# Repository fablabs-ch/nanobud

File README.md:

# Description
NanoBud is a simple electronic project created for workshops into FabLabs.
Basically this project is provided with "Space Invaders" retro game made by makestuffordie.
With simple electronic components you can make some great stuffs.
But you can use it not only for gaming. 
Per example, replace the rotary encoder by a temperature sensor, load the suitable arduino sketch, then you have a beautiful portable weather station!

With this project you can do a workshop and show people how to assembly electronic components and get perfect welds. 
Please visit the wiki to get the workshop kit. -> [Wiki](https://github.com/fablabs-ch/nanobud/wiki)

But not only, if you want go further and make different kind of workshops, here some quick ideas:
- How to load and programm Arduino boards
- How to manage oled screen.
- Design your own case for 3D print or 2D Lasercut.

As you understood, the only limit is your creativity. :-)

Enjoy and don't hesitate to share your experiences.

# Hardware
## Material
*Version 1*
- 1x Rotary encoder
- 1x Arduino Nano
- 1x OLED screen 0.96" 128x64pix
- 1x micro switch
- 1x 9V Battery
- 1x 9V  to wire adapter
- 1x Buzzer
- 1x Resistor 100 Ohms
- 1x Female pin header	1x4

*Black edition*
- 1x Female pin header	1x4
- 1x Arduino Nano
- 1x OLED screen 0.96" 128x64pix
- 1x micro switch
- 1x 9V Battery
- 1x 9V  to wire adapter
- 1x Buzzer
- 1x Resistor 100 Ohms
- **1x Capacitor 100pF**
- **1x Shotkky diode	1N5819**
- **1x Vibrator	3.3V**
- **1x Resistor	300 Ohms**
- **1x Resistor	10k**
- **1x MOSFET	BS170**
- **1x Mini Joystick**	
- **1x Battery holder 9V**
- **1x ScrewVis M2.5 x8mm**	
- **1 PCB black**

# Software
The version 1 is the sketch from makestuffordie
Black edition need the software made for. sotware/nanobud. It will manage the vibrator and the joystick

Improvements or other applications would be appreciated. Don't hesitate to share it!
Don't hesitate participate to the project.

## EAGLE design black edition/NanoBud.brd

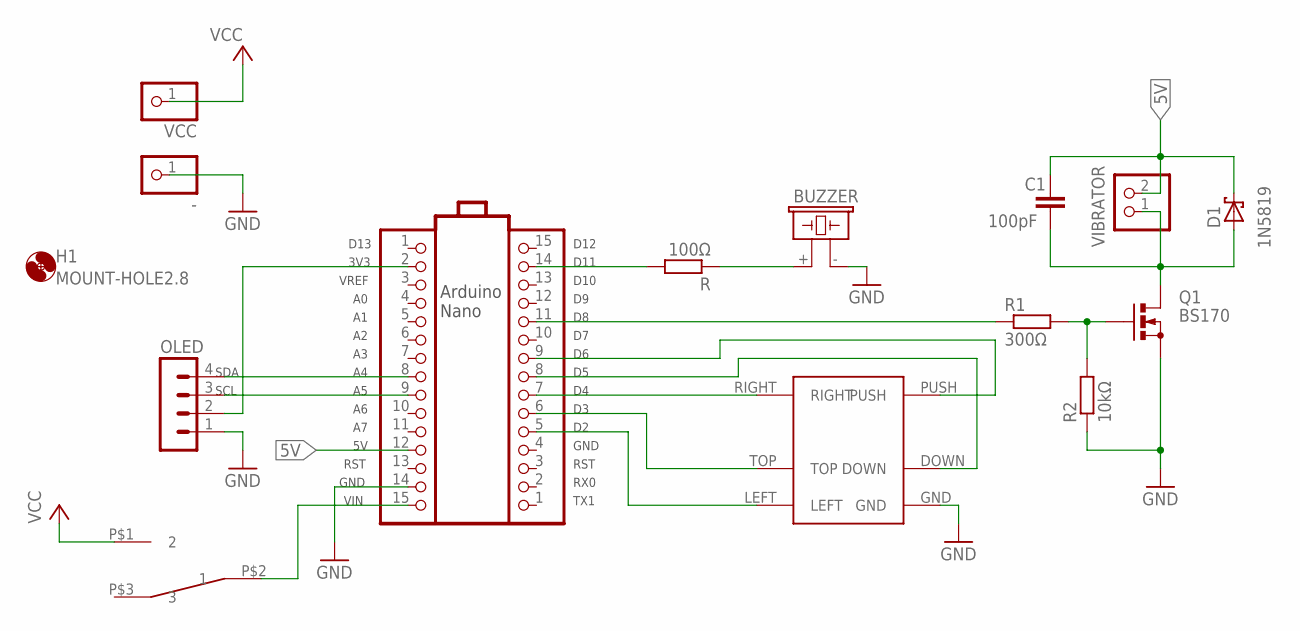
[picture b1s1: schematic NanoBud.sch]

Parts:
-: PINHD-1X1; 1X01
BUZZER: F/CM12P
C1: 100pF; C2.5-2
D1: BAT49; DO41-10
H1: MOUNT-HOLE2.8; 2,8
OLED: MA04-1
Q1: BS170; SOT54E
R: 100Ω; 0204/7
R1: 300Ω; 0204/7
R2: 10kΩ; 0204/7
SV1, SV2: PINHD-1X15; 1X15
U$1: SWITCHCHINOIS
U$2: MOMENTARYBUTTON
VCC: PINHD-1X1; 1X01
VIBRATOR: PINHD-1X2; 1X02

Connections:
3V3: OLED.2, SV2.2
5V: C1.1, D1.C, SV2.12, VIBRATOR.2
GND: -.1, BUZZER.- (2), OLED.1, Q1.S, R2.1, SV2.14, U$2.GND
unnamed: SV1.5, U$2.LEFT
unnamed: SV1.6, U$2.TOP
unnamed: SV1.7, U$2.RIGHT
unnamed: SV1.8, U$2.DOWN
unnamed: SV1.9, U$2.PUSH
unnamed: OLED.3, SV2.9
unnamed: OLED.4, SV2.8
unnamed: BUZZER.+ (1), R.1
unnamed: R.2, SV1.14
unnamed: SV2.15, U$1.P$2 (1)
unnamed: R1.1, SV1.11
unnamed: Q1.G, R1.2, R2.2
unnamed: C1.2, D1.A, Q1.D, VIBRATOR.1
VCC: U$1.P$1 (2), VCC.1

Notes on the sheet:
SDA
SCL
D13
3V3
VREF
RST
GND
VIN
TX1
RX0
D10
D11
D12
Arduino Nano
1N5819

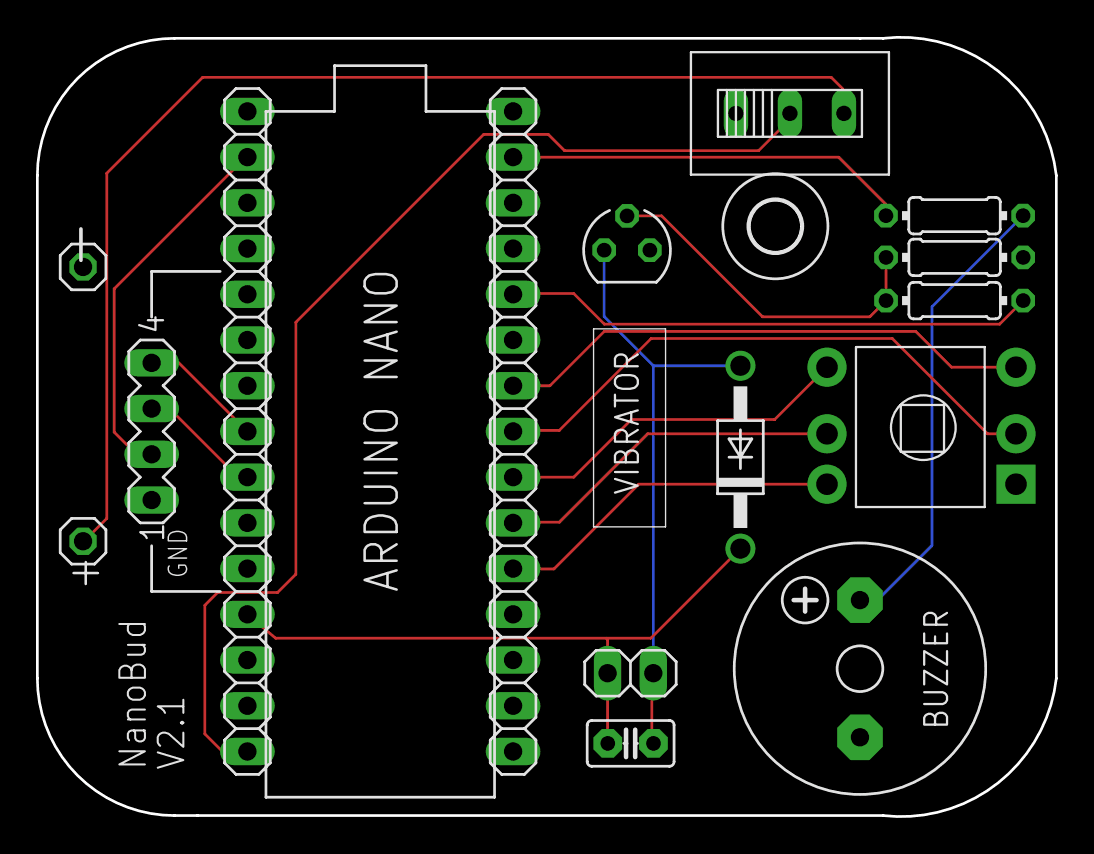
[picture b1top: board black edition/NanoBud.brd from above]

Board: 2 copper layers, 56.6 x 43.3 mm, 16 parts (0 on the bottom side), 17 nets.

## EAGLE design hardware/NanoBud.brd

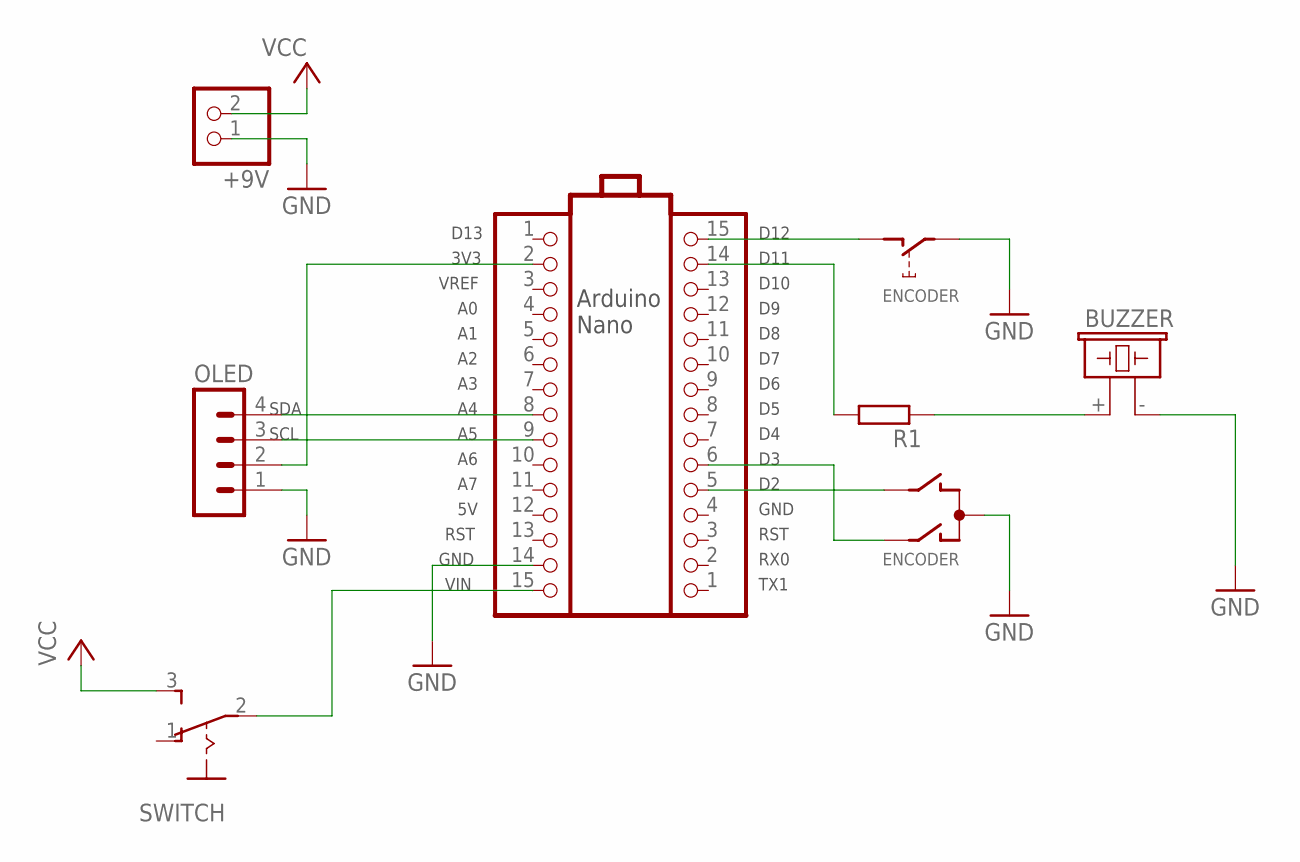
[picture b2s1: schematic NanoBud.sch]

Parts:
+9V: PINHD-1X2; 1X02
BUZZER: F/CM12P
ENCODER: EC12E_SW; ALPS_EC12E_SW
OLED: MA04-1
R1: R0204/7; 0204/7
SV1, SV2: PINHD-1X15; 1X15
SWITCH: M251

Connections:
GND: +9V.1, BUZZER.- (2), ENCODER.C, ENCODER.E (2), OLED.1, SV2.14
unnamed: ENCODER.A, SV1.6
unnamed: ENCODER.D (1), SV1.15
unnamed: ENCODER.B, SV1.5
unnamed: OLED.2, SV2.2
unnamed: OLED.3, SV2.9
unnamed: OLED.4, SV2.8
unnamed: BUZZER.+ (1), R1.1
unnamed: R1.2, SV1.14
unnamed: SV2.15, SWITCH.2
VCC: +9V.2, SWITCH.3 (S)

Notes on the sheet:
SDA
SCL
D13
3V3
VREF
RST
GND
VIN
TX1
RX0
D10
D11
D12
Arduino Nano

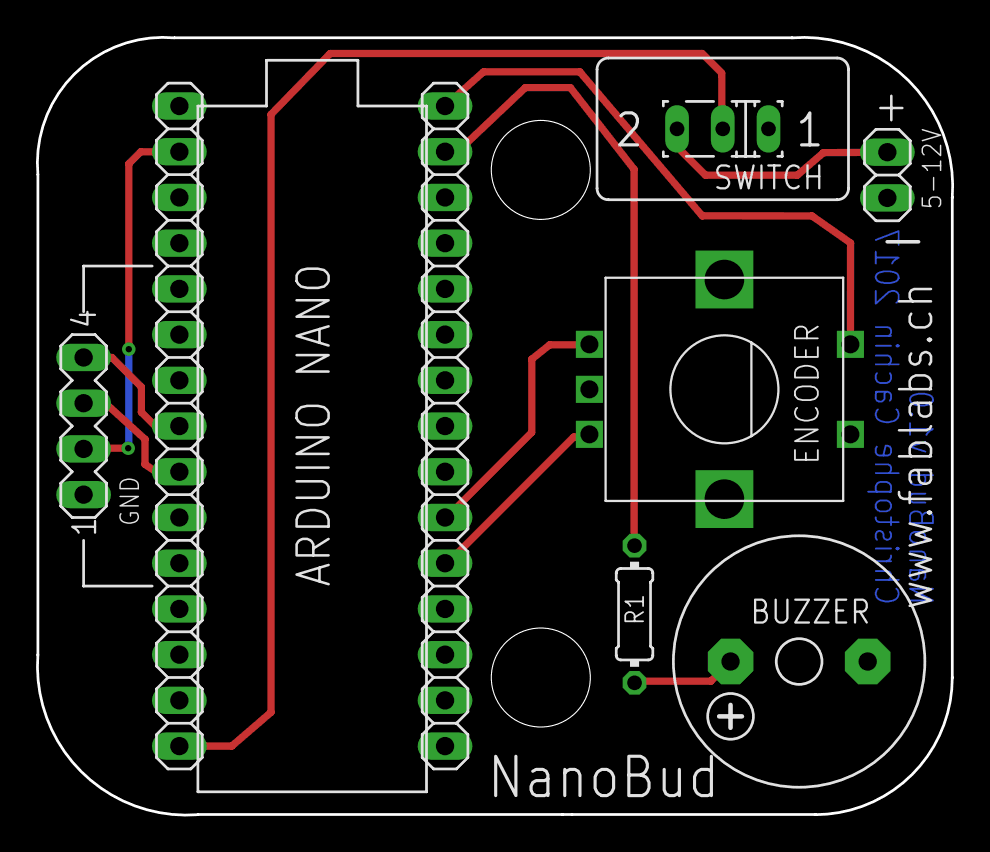
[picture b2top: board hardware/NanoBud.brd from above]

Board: 2 copper layers, 50.9 x 43.2 mm, 8 parts (0 on the bottom side), 11 nets.

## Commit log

2017-08-17 Content in progress
    Hardware/Software files
2017-08-17 logo size
2017-08-17 Update
    Readme
    Arduino sketch
2017-08-17 add wiki link
2017-08-17 pictures for welding station
2017-08-18 Hardware files
2017-08-18 dimension update
2017-08-18 pics for wiki
2017-08-21 logo
2017-08-23 new pictures
2017-08-23 readme
2017-08-23 size readme
2017-08-23 minor
2017-08-23 size
2017-08-23 size logos
2017-08-23 syntax
2017-08-25 Add tone on buzzer
    And reset when game is done
2017-08-27 initial project
2017-08-27 pwew pwew
2017-08-27 rotary by interrupt
2017-08-27 it's a bird
2017-08-27 ghost busters
2017-08-28 hit box
2017-08-28 fix sound
2017-09-03 game states loop
2017-09-03 game state init
2017-09-10 encoder knob
2018-06-19 joystick
2018-07-15 vibrator
2018-08-16 splash and button
2018-08-16 up to fire
2018-08-20 levels
2018-08-22 black edition
    adding:
    - joystick
    - vibrator
    - battery holder
2018-08-22 new picts
    new pictures for black edition and assembly instructions
2018-08-26 increase difficulty
2018-10-17 Update
    joystick .stl
    new instructions
2018-10-17 schematic
2018-10-28 start of snake
2018-11-01 snake game
2018-11-18 Migrate from U8glib to U8g2
2018-11-18 working splash image logo
2018-11-18 make GameState a class enum for namespacing
2018-11-18 create a game interface and a menu game which can start other games
    Works but if both games are included there is not enough memory for snake to start?
2018-11-18 switching to 1 line page buffer to reduce memory usage
2018-11-18 using a _tr (transparent + reduced) font to reduce program memory
